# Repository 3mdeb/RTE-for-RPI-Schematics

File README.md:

# Schematics of the RTE platform for Raspberry Pi

This repository contains source files for Remote Testing Environment schematics.

If you want to read more about this project, here are some useful links:

* Firmware/software:
  - meta-rte - custom firmware for RTE RPi [TBD]
  - [RteCtrl](https://github.com/3mdeb/RteCtrl) - binary for power management on
  board ([MIT license](https://github.com/3mdeb/RteCtrl/blob/master/LICENSE))
* Datasheet (under CC BY-SA 4.0 International License):
  - [RTE RPi v0.1.2 datasheet](https://cloud.3mdeb.com/index.php/s/cM5Mi4w2mjKNpBY)

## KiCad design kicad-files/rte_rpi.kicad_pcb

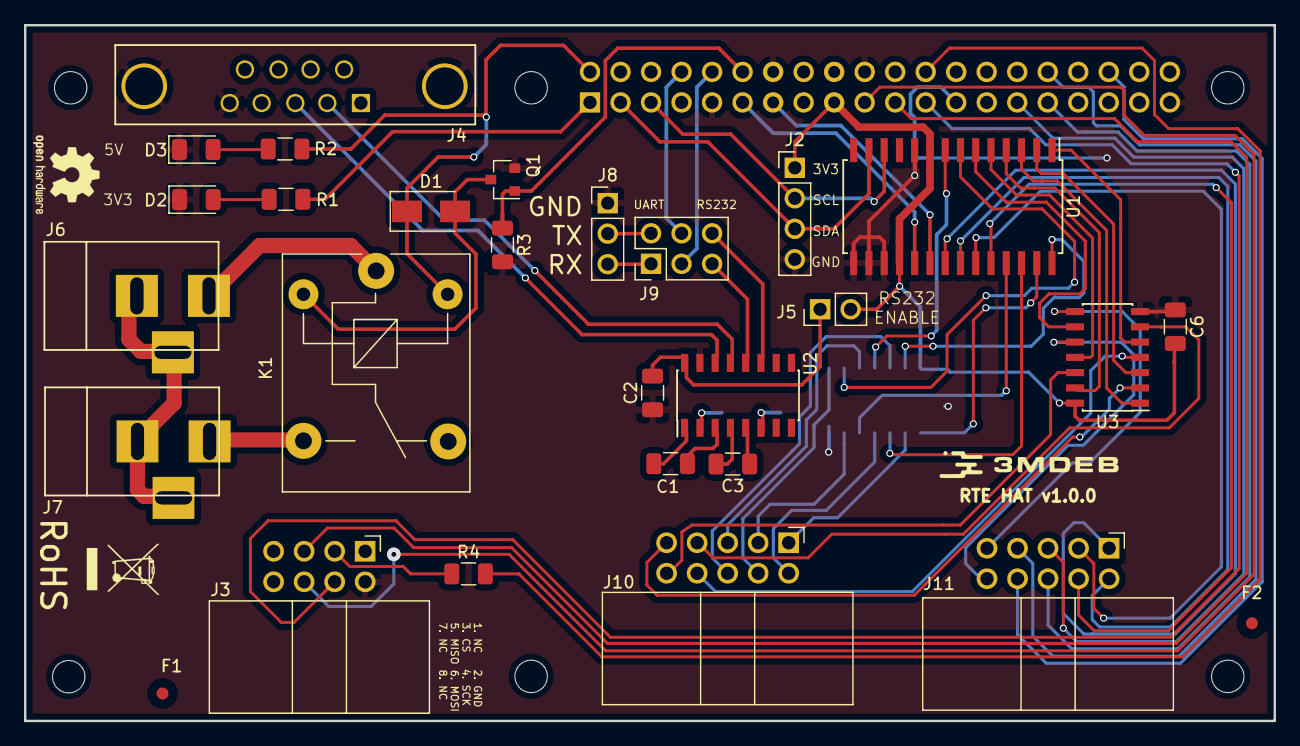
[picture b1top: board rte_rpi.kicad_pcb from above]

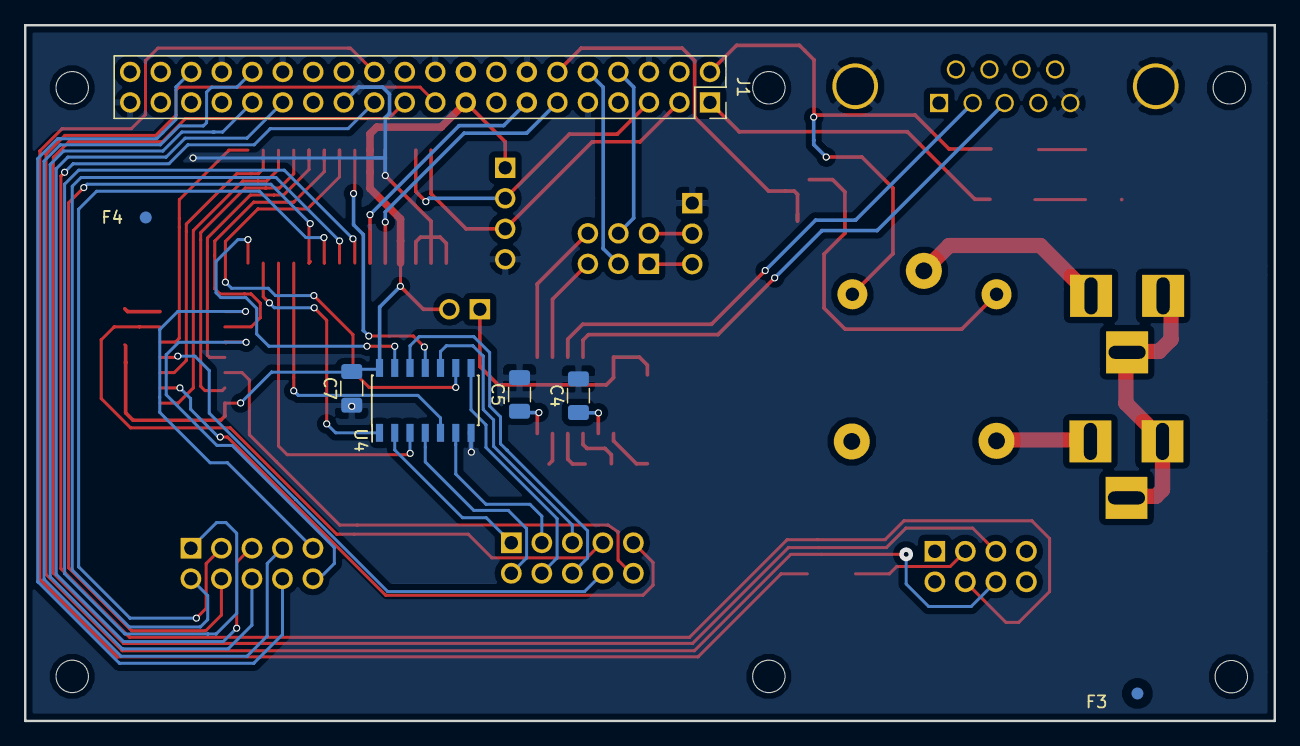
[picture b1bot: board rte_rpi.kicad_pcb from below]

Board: 2 copper layers, 104.0 x 57.9 mm, 42 parts (5 on the bottom side), 66 nets.

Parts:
C1, C2, C3, C4, C5, C6, C7: 100nF; C_1206_3216Metric
D1: S1A-E3/61T; D_SMA
D2: Orange LED 3V3; LED_1206_3216Metric
D3: Red LED 5V; LED_1206_3216Metric
F1, F2: Fiducial_1mm_Dia_2.54mm_Outer_CopperTop
F3, F4: Fiducial_1mm_Dia_2.54mm_Outer_CopperBottom
G1: 3MDEB_LOGO; 3mdeb_logo
J1: Raspberry Pi 3 Header; PinSocket_2x20_P2.54mm_Vertical
J2: I2C Header; PinHeader_1x04_P2.54mm_Vertical
J3: SPI Header; IDC-Header_2x04_P2.54mm_Horizontal
J4: RS232 OUT; DB9MD
J5: UART Enable; PinHeader_1x02_P2.54mm_Vertical
J6: DUT Power Supply Input; BARREL_JACK
J7: DUT Power Supply Output; BARREL_JACK
J8: EXT UART; PinHeader_1x03_P2.54mm_Vertical
J9: UART_HEADER; PinHeader_2x03_P2.54mm_Vertical
J10, J11: OC_BUFFER_OUTPUT_HEADER; IDC-Header_2x05_P2.54mm_Horizontal
K1: HF3FA; Relay_SPDT_SANYOU_SRD_Series_Form_C
MK1, MK2, MK3, MK4, MK5, MK6: Mounting_Hole; MountingHole_2.7mm
Q1: NDS351AN; SOT-23
R1, R2, R4: 1k; R_1206_3216Metric
R3: 10k; R_1206_3216Metric
U1: MCP23017; SOIC-28W_7.5x17.9mm_P1.27mm
U2: MAX3232; SOIC-16_3.9x9.9mm_P1.27mm
U3, U4: 74LS06; SOIC-14_3.9x8.7mm_P1.27mm

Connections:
+3V3: C6.2, C7.2, J1.1, J1.17, J2.1, J5.2, R1.1, U1.9, U1.18, U3.14, U4.14
+5V: D1.1, J1.2, J1.4, K1.5, R2.1
DUT_CLR: J11.10, U3.10
DUT_MODESW: J10.10, U3.12
DUT_PWR: J10.9, U3.2
DUT_RST: J10.8, U3.4
DUT_WDT: J10.7, U3.6
DUT_WP: J11.9, U3.8
GND: C2.1, C4.2, C5.2, C6.1, C7.1, D2.1, D3.1, J1.6, J1.9, J1.14, J1.20, J1.25, J1.30, J1.34, J1.39, J2.4, J3.2, J4.0, J4.5, J8.1, Q1.2, R3.2, U1.10, U1.15, U1.16, U1.17, U2.15, U3.7, U4.7
GPA0: J11.1, U1.21
GPA1: J11.2, U1.22
GPA2: J11.3, U1.23
GPA3: J11.4, U1.24
GPA4: U1.25, U4.5
GPA5: U1.26, U4.3
GPA6: U1.27, U4.1
GPA7: U1.28, U4.13
GPB0: U1.1, U3.5
GPB1: U1.2, U3.3
GPB2: U1.3, U3.1
GPB3: U1.4, U3.13
GPB4: U1.5, U3.11
GPB5: U1.6, U3.9
GPB6: U1.7, U4.9
GPB7: U1.8, U4.11
GPIO_1: J1.29, J11.5
GPIO_2: J1.31, J11.6
GPIO_3: J1.32, J11.7
GPIO_4: J1.36, J11.8
I2C_SCL: J1.5, J2.2, U1.12
I2C_SDA: J1.3, J2.3, U1.13
INTA: J1.13, U1.20
INTB: J1.11, U1.19
unnamed: C1.1, U2.1
unnamed: C1.2, U2.3
unnamed: C2.2, J5.1, U2.16
unnamed: C3.1, U2.5
unnamed: C3.2, U2.4
unnamed: C4.1, U2.2
unnamed: C5.1, U2.6
unnamed: D1.2, K1.2, Q1.3
unnamed: D2.2, R1.2
unnamed: D3.2, R2.2
unnamed: J3.3, R4.1
unnamed: J6.1, K1.1
unnamed: J6.2, J6.3, J7.2, J7.3
unnamed: J7.1, K1.3
OC_OUT1: J10.1, U4.2
OC_OUT2: J10.2, U4.4
OC_OUT3: J10.3, U4.6
OC_OUT4: J10.4, U4.8
OC_OUT5: J10.5, U4.10
OC_OUT6: J10.6, U4.12
RELAY_CTR: J1.12, Q1.1, R3.1
RS232_RX: J4.2, U2.13
RS232_TX: J4.3, U2.14
SPI_CE0: J1.24, R4.2
SPI_MISO: J1.21, J3.5
SPI_MOSI: J1.19, J3.6
SPI_SCK: J1.23, J3.4
UART_RX_EXT: J8.3, J9.1
UART_RX_RPI: J1.10, J9.3
UART_RX_RS232: J9.E, U2.12
UART_TX_EXT: J8.2, J9.2
UART_TX_RPI: J1.8, J9.4
UART_TX_RS232: J9.6, U2.11

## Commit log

2018-09-17 Added initial version of RTE for RPi
2018-09-17 Modified changelog
2018-09-17 Removed some rescue files
2020-03-18 add rte-rpi-schematics-v1.0.0.pdf
2020-04-01 add CERN LICENSE.txt file
2020-04-01 README.md: add licenses description
2022-03-04 README.md: Fix specification link
